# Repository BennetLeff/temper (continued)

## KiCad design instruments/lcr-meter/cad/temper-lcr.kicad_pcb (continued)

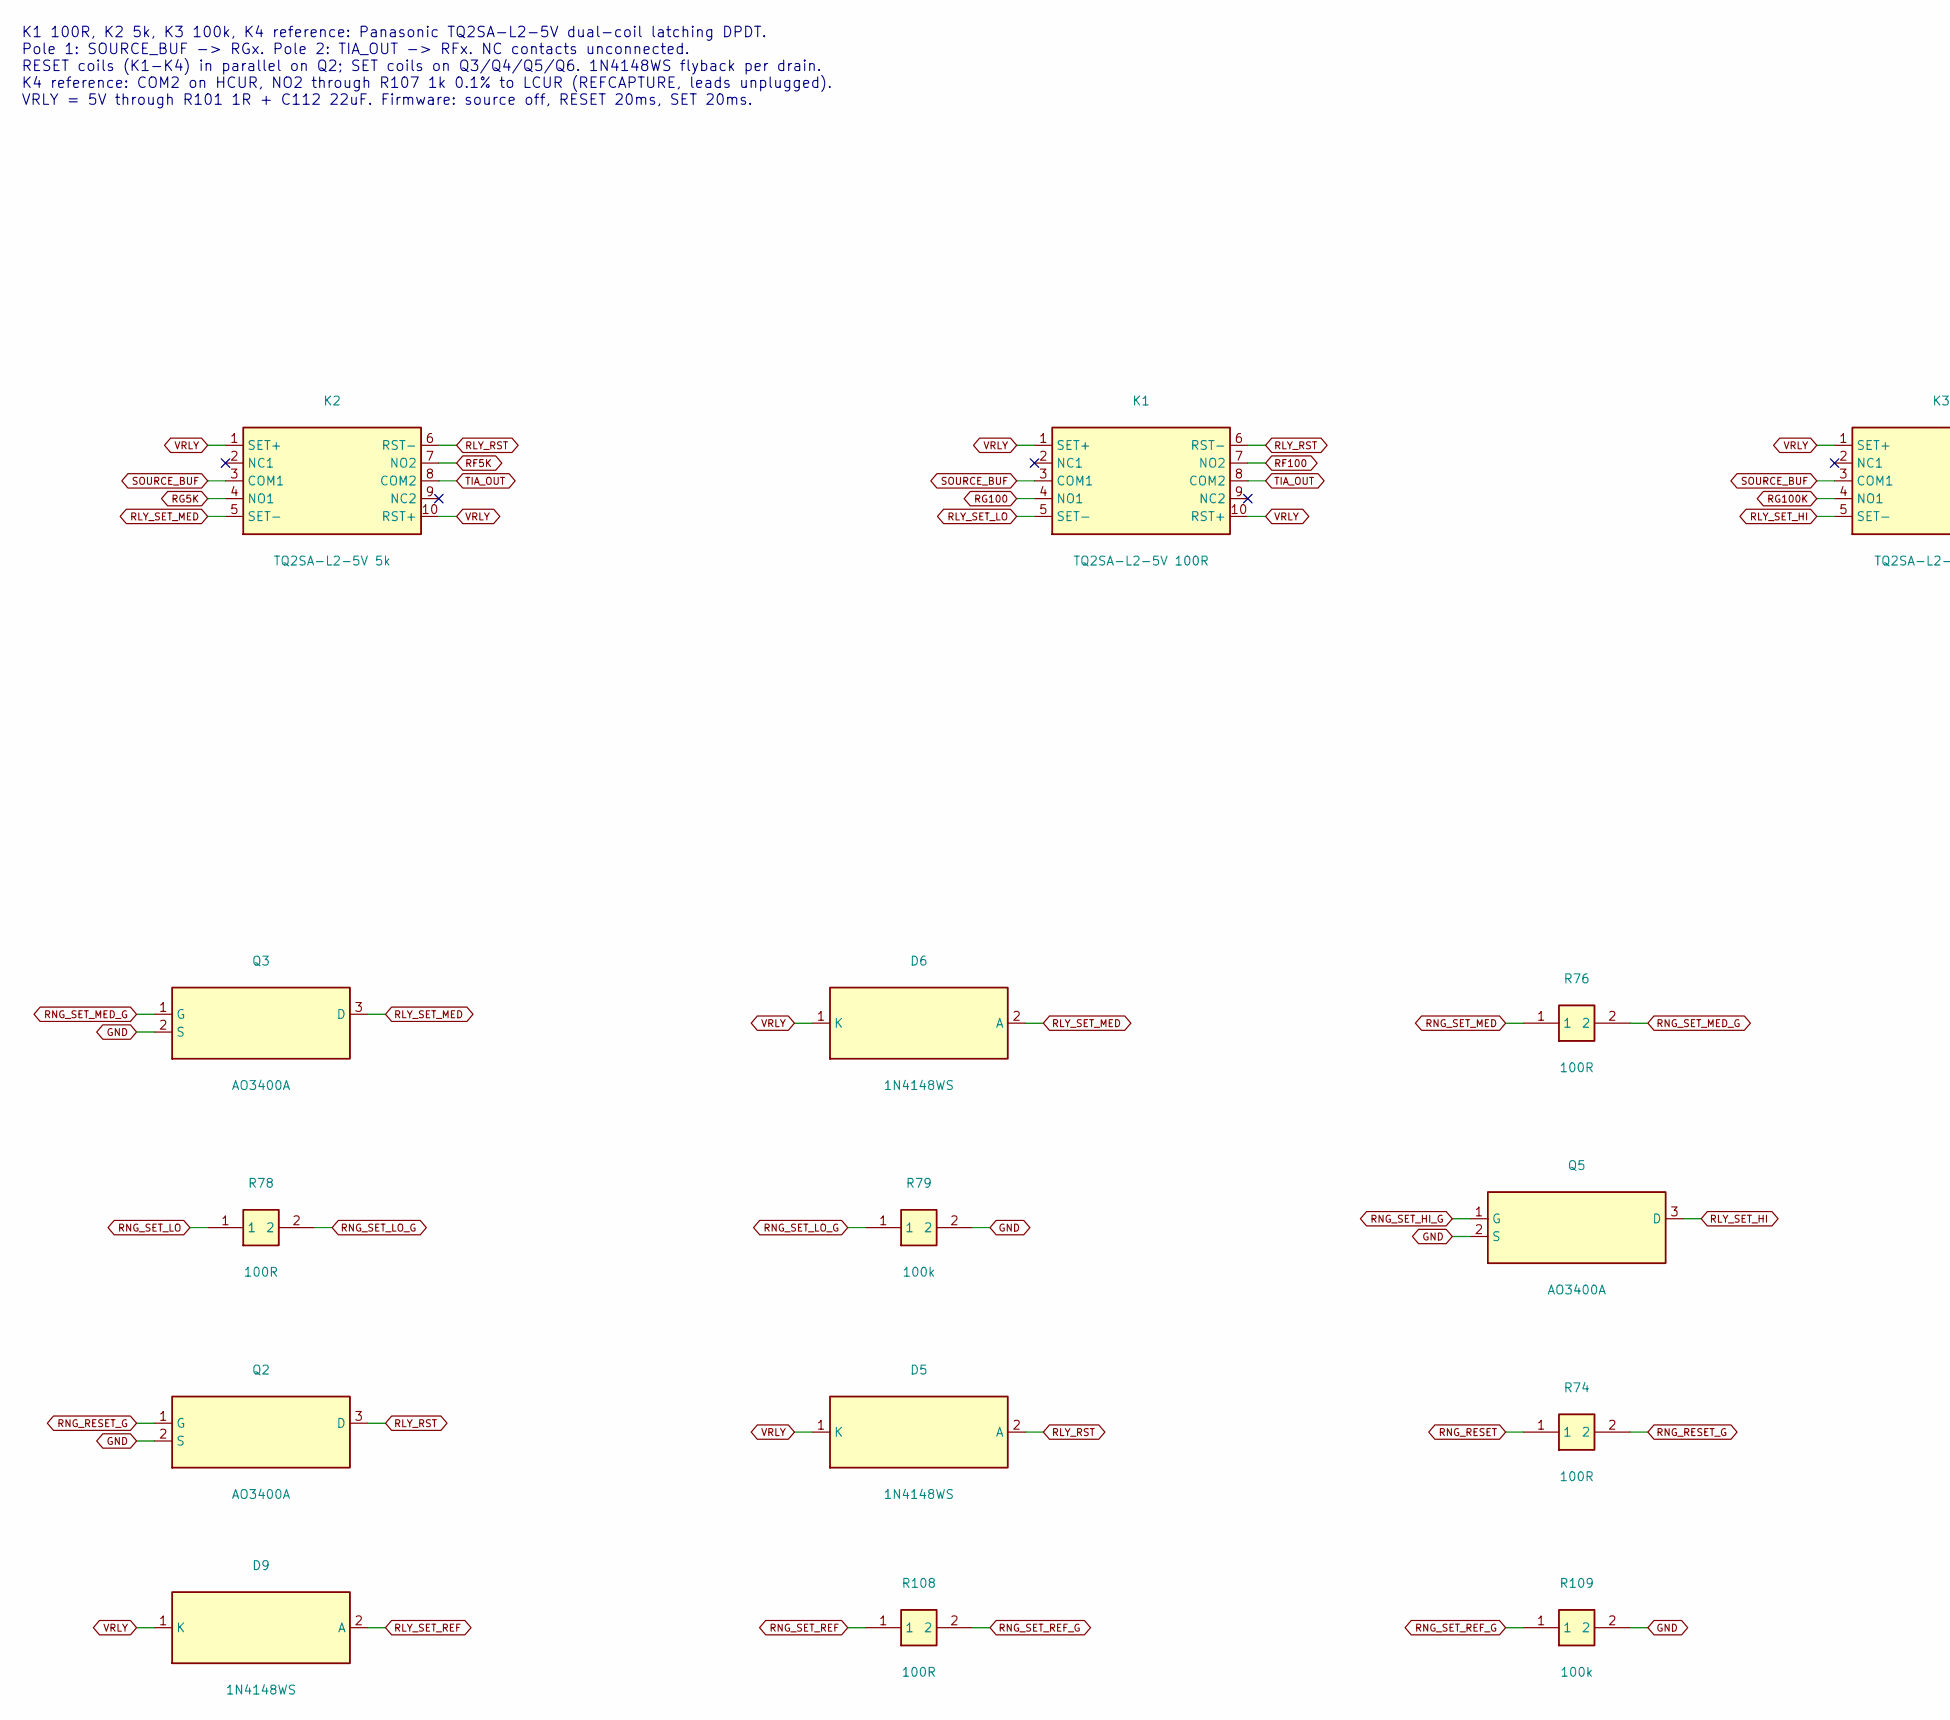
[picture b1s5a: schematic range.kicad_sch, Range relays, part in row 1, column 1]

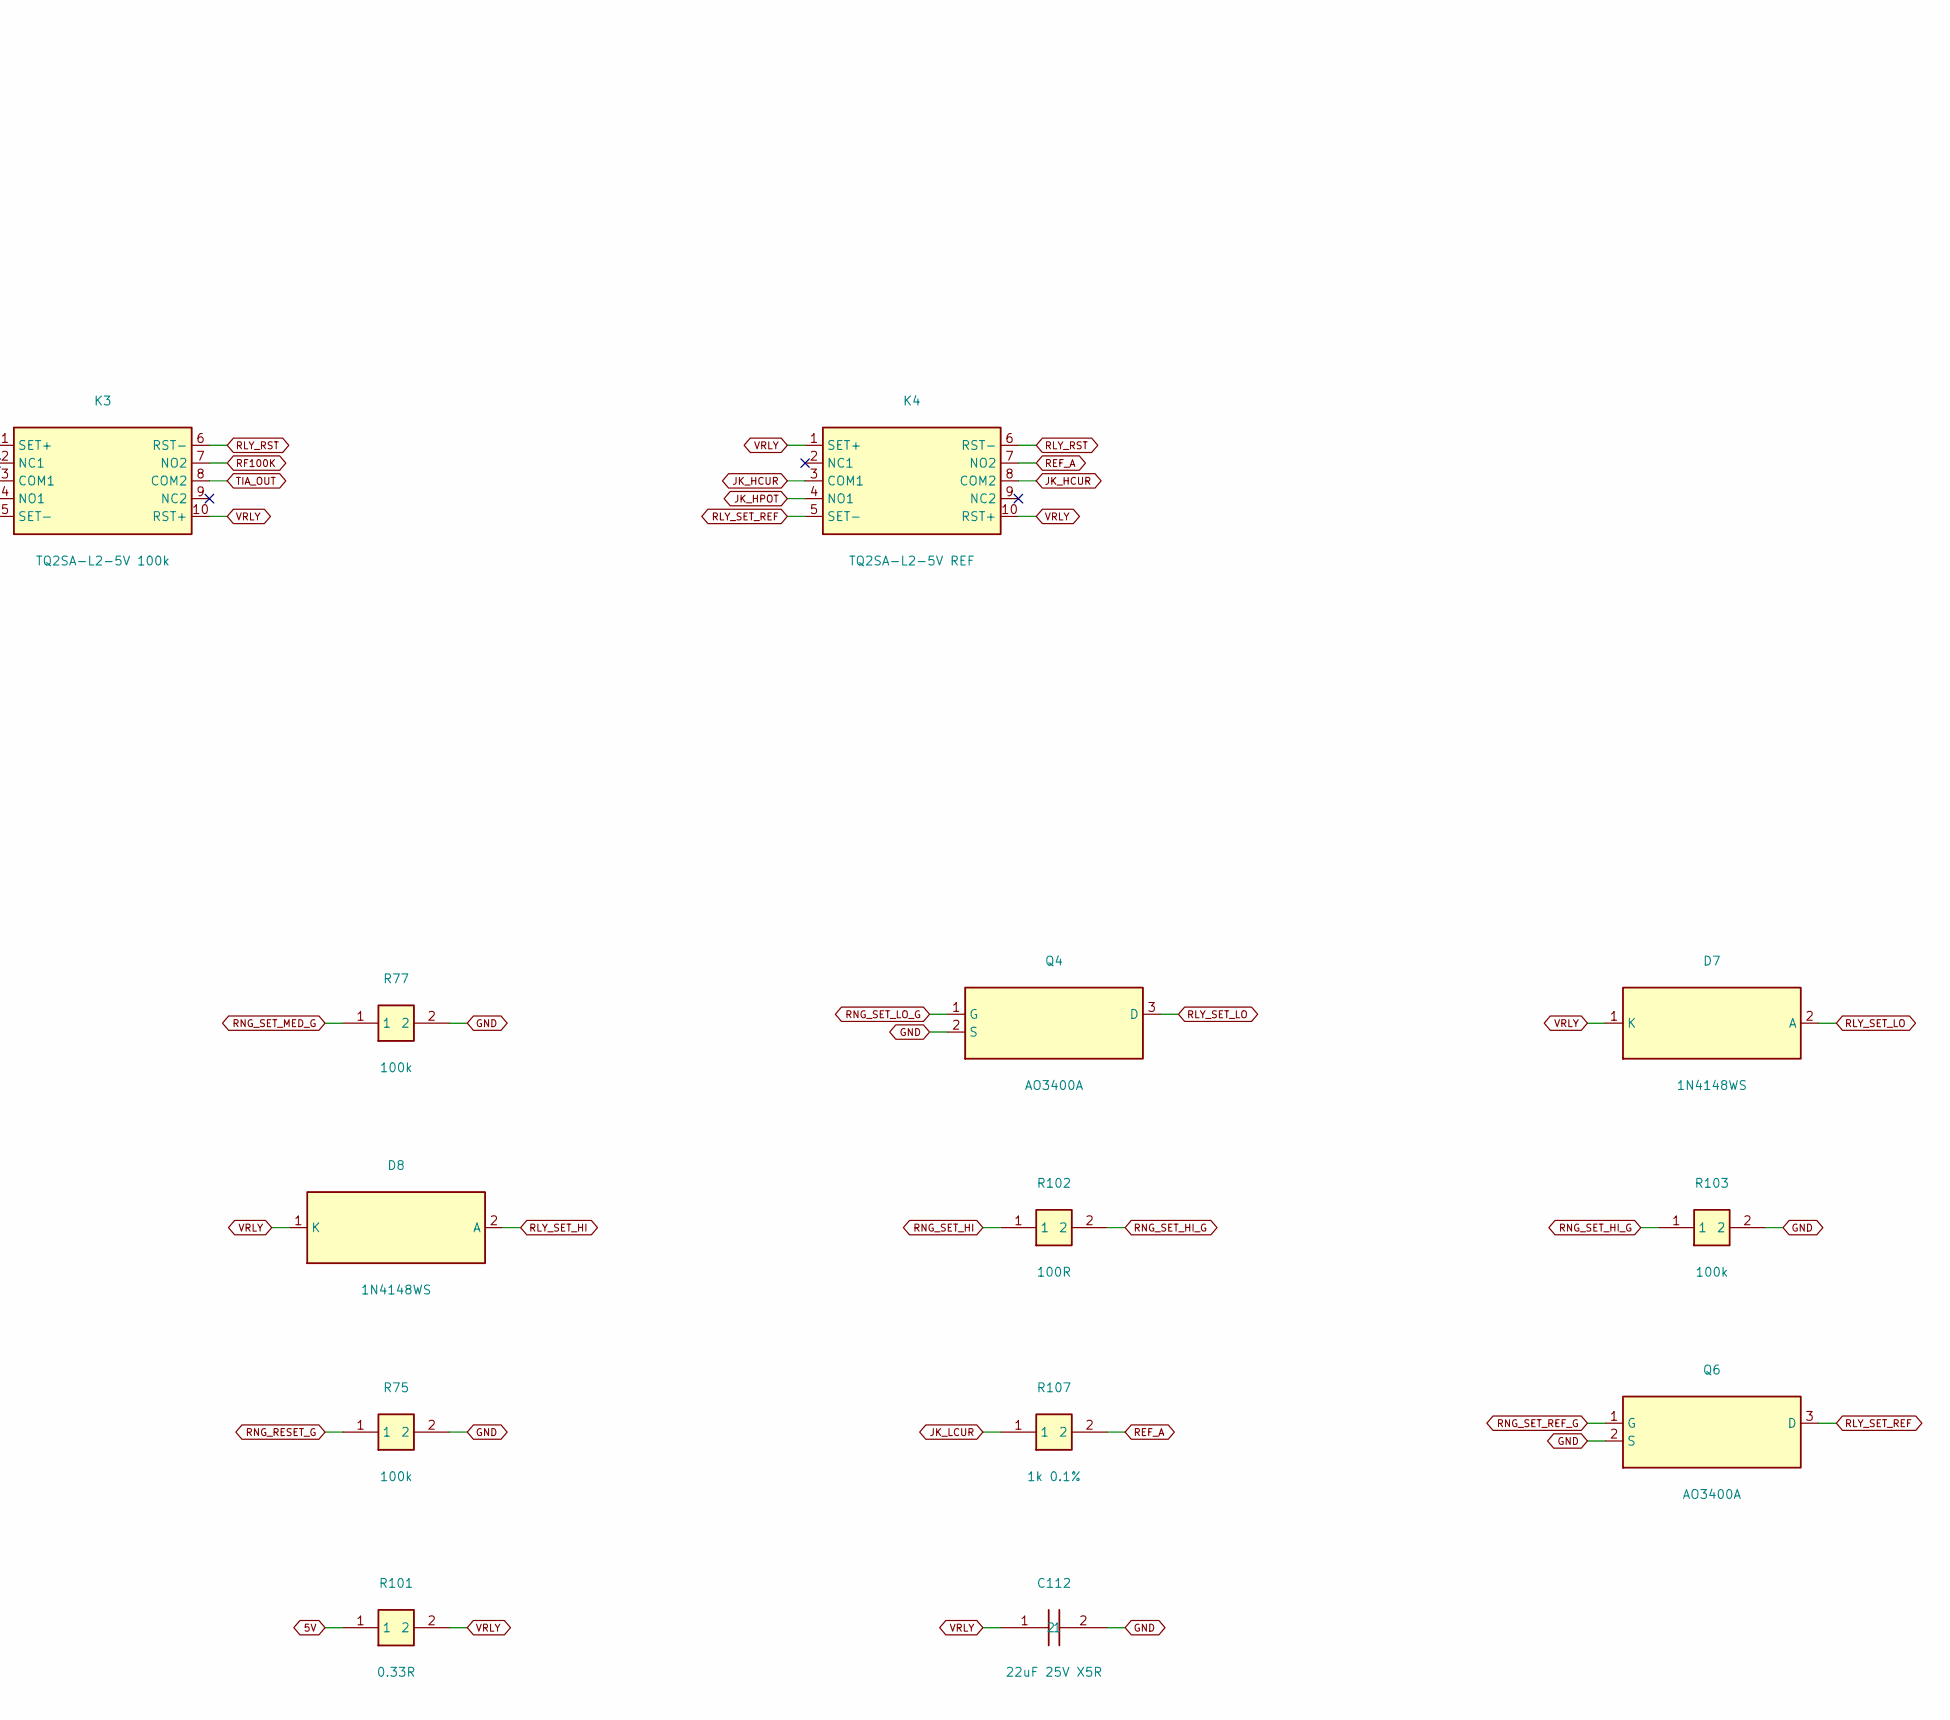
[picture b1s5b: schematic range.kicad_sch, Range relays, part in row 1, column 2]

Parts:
C112: 22uF 25V X5R; C_1206_3216Metric; MPN CL31A226KAHNNNE; LCSC C12891
D5, D6, D7, D8, D9: 1N4148WS; D_SOD-323; MPN 1N4148WS; LCSC C2128
K1: TQ2SA-L2-5V 100R; Relay_DPDT_Panasonic_TQ2SA_SMD; MPN TQ2SA-L2-5V-Z; LCSC C2684450
K2: TQ2SA-L2-5V 5k; Relay_DPDT_Panasonic_TQ2SA_SMD; MPN TQ2SA-L2-5V-Z; LCSC C2684450
K3: TQ2SA-L2-5V 100k; Relay_DPDT_Panasonic_TQ2SA_SMD; MPN TQ2SA-L2-5V-Z; LCSC C2684450
K4: TQ2SA-L2-5V REF; Relay_DPDT_Panasonic_TQ2SA_SMD; MPN TQ2SA-L2-5V-Z; LCSC C2684450
Q2, Q3, Q4, Q5, Q6: AO3400A; SOT-23; MPN AO3400A; LCSC C20917
R74, R76, R78, R102, R108: 100R; R_0603_1608Metric; MPN 0603WAF1000T5E; LCSC C22775
R75, R77, R79, R103, R109: 100k; R_0603_1608Metric; MPN 0603WAF1003T5E; LCSC C25803
R101: 0.33R; R_0603_1608Metric; MPN 0603WAF330LT5E; LCSC C23410
R107: 1k 0.1%; R_0603_1608Metric; MPN RT0603BRD071KL; LCSC C110776

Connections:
5V: R101.1; also elsewhere on the board
GND: C112.2, Q2.2 (S), Q3.2 (S), Q4.2 (S), Q5.2 (S), Q6.2 (S), R75.2, R77.2, R79.2, R103.2, R109.2; also elsewhere on the board
JK_HCUR: K4.3 (COM1), K4.8 (COM2); also elsewhere on the board
JK_HPOT: K4.4 (NO1); also elsewhere on the board
JK_LCUR: R107.1; also elsewhere on the board
REF_A: K4.7 (NO2), R107.2
RF5K: K2.7 (NO2); also elsewhere on the board
RF100: K1.7 (NO2); also elsewhere on the board
RF100K: K3.7 (NO2); also elsewhere on the board
RG5K: K2.4 (NO1); also elsewhere on the board
RG100: K1.4 (NO1); also elsewhere on the board
RG100K: K3.4 (NO1); also elsewhere on the board
RLY_RST: D5.2 (A), K1.6 (RST-), K2.6 (RST-), K3.6 (RST-), K4.6 (RST-), Q2.3 (D); also elsewhere on the board
RLY_SET_HI: D8.2 (A), K3.5 (SET-), Q5.3 (D); also elsewhere on the board
RLY_SET_LO: D7.2 (A), K1.5 (SET-), Q4.3 (D); also elsewhere on the board
RLY_SET_MED: D6.2 (A), K2.5 (SET-), Q3.3 (D); also elsewhere on the board
RLY_SET_REF: D9.2 (A), K4.5 (SET-), Q6.3 (D); also elsewhere on the board
RNG_RESET: R74.1; also elsewhere on the board
RNG_RESET_G: Q2.1 (G), R74.2, R75.1
RNG_SET_HI: R102.1; also elsewhere on the board
RNG_SET_HI_G: Q5.1 (G), R102.2, R103.1
RNG_SET_LO: R78.1; also elsewhere on the board
RNG_SET_LO_G: Q4.1 (G), R78.2, R79.1
RNG_SET_MED: R76.1; also elsewhere on the board
RNG_SET_MED_G: Q3.1 (G), R76.2, R77.1
RNG_SET_REF: R108.1; also elsewhere on the board
RNG_SET_REF_G: Q6.1 (G), R108.2, R109.1
SOURCE_BUF: K1.3 (COM1), K2.3 (COM1), K3.3 (COM1); also elsewhere on the board
TIA_OUT: K1.8 (COM2), K2.8 (COM2), K3.8 (COM2); also elsewhere on the board
VRLY: C112.1, D5.1 (K), D6.1 (K), D7.1 (K), D8.1 (K), D9.1 (K), K1.1 (SET+), K1.10 (RST+), K2.1 (SET+), K2.10 (RST+), K3.1 (SET+), K3.10 (RST+), K4.1 (SET+), K4.10 (RST+), R101.2; also elsewhere on the board

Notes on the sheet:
K1 100R, K2 5k, K3 100k, K4 reference: Panasonic TQ2SA-L2-5V dual-coil latching DPDT. Pole 1: SOURCE_BUF -> RGx. Pole 2: TIA_OUT -> RFx. NC contacts unconnected. RESET coils (K1-K4) in parallel on Q2; SET coils on Q3/Q4/Q5/Q6. 1N4148WS flyback per drain. K4 reference: COM2 on HCUR, NO2 through R107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

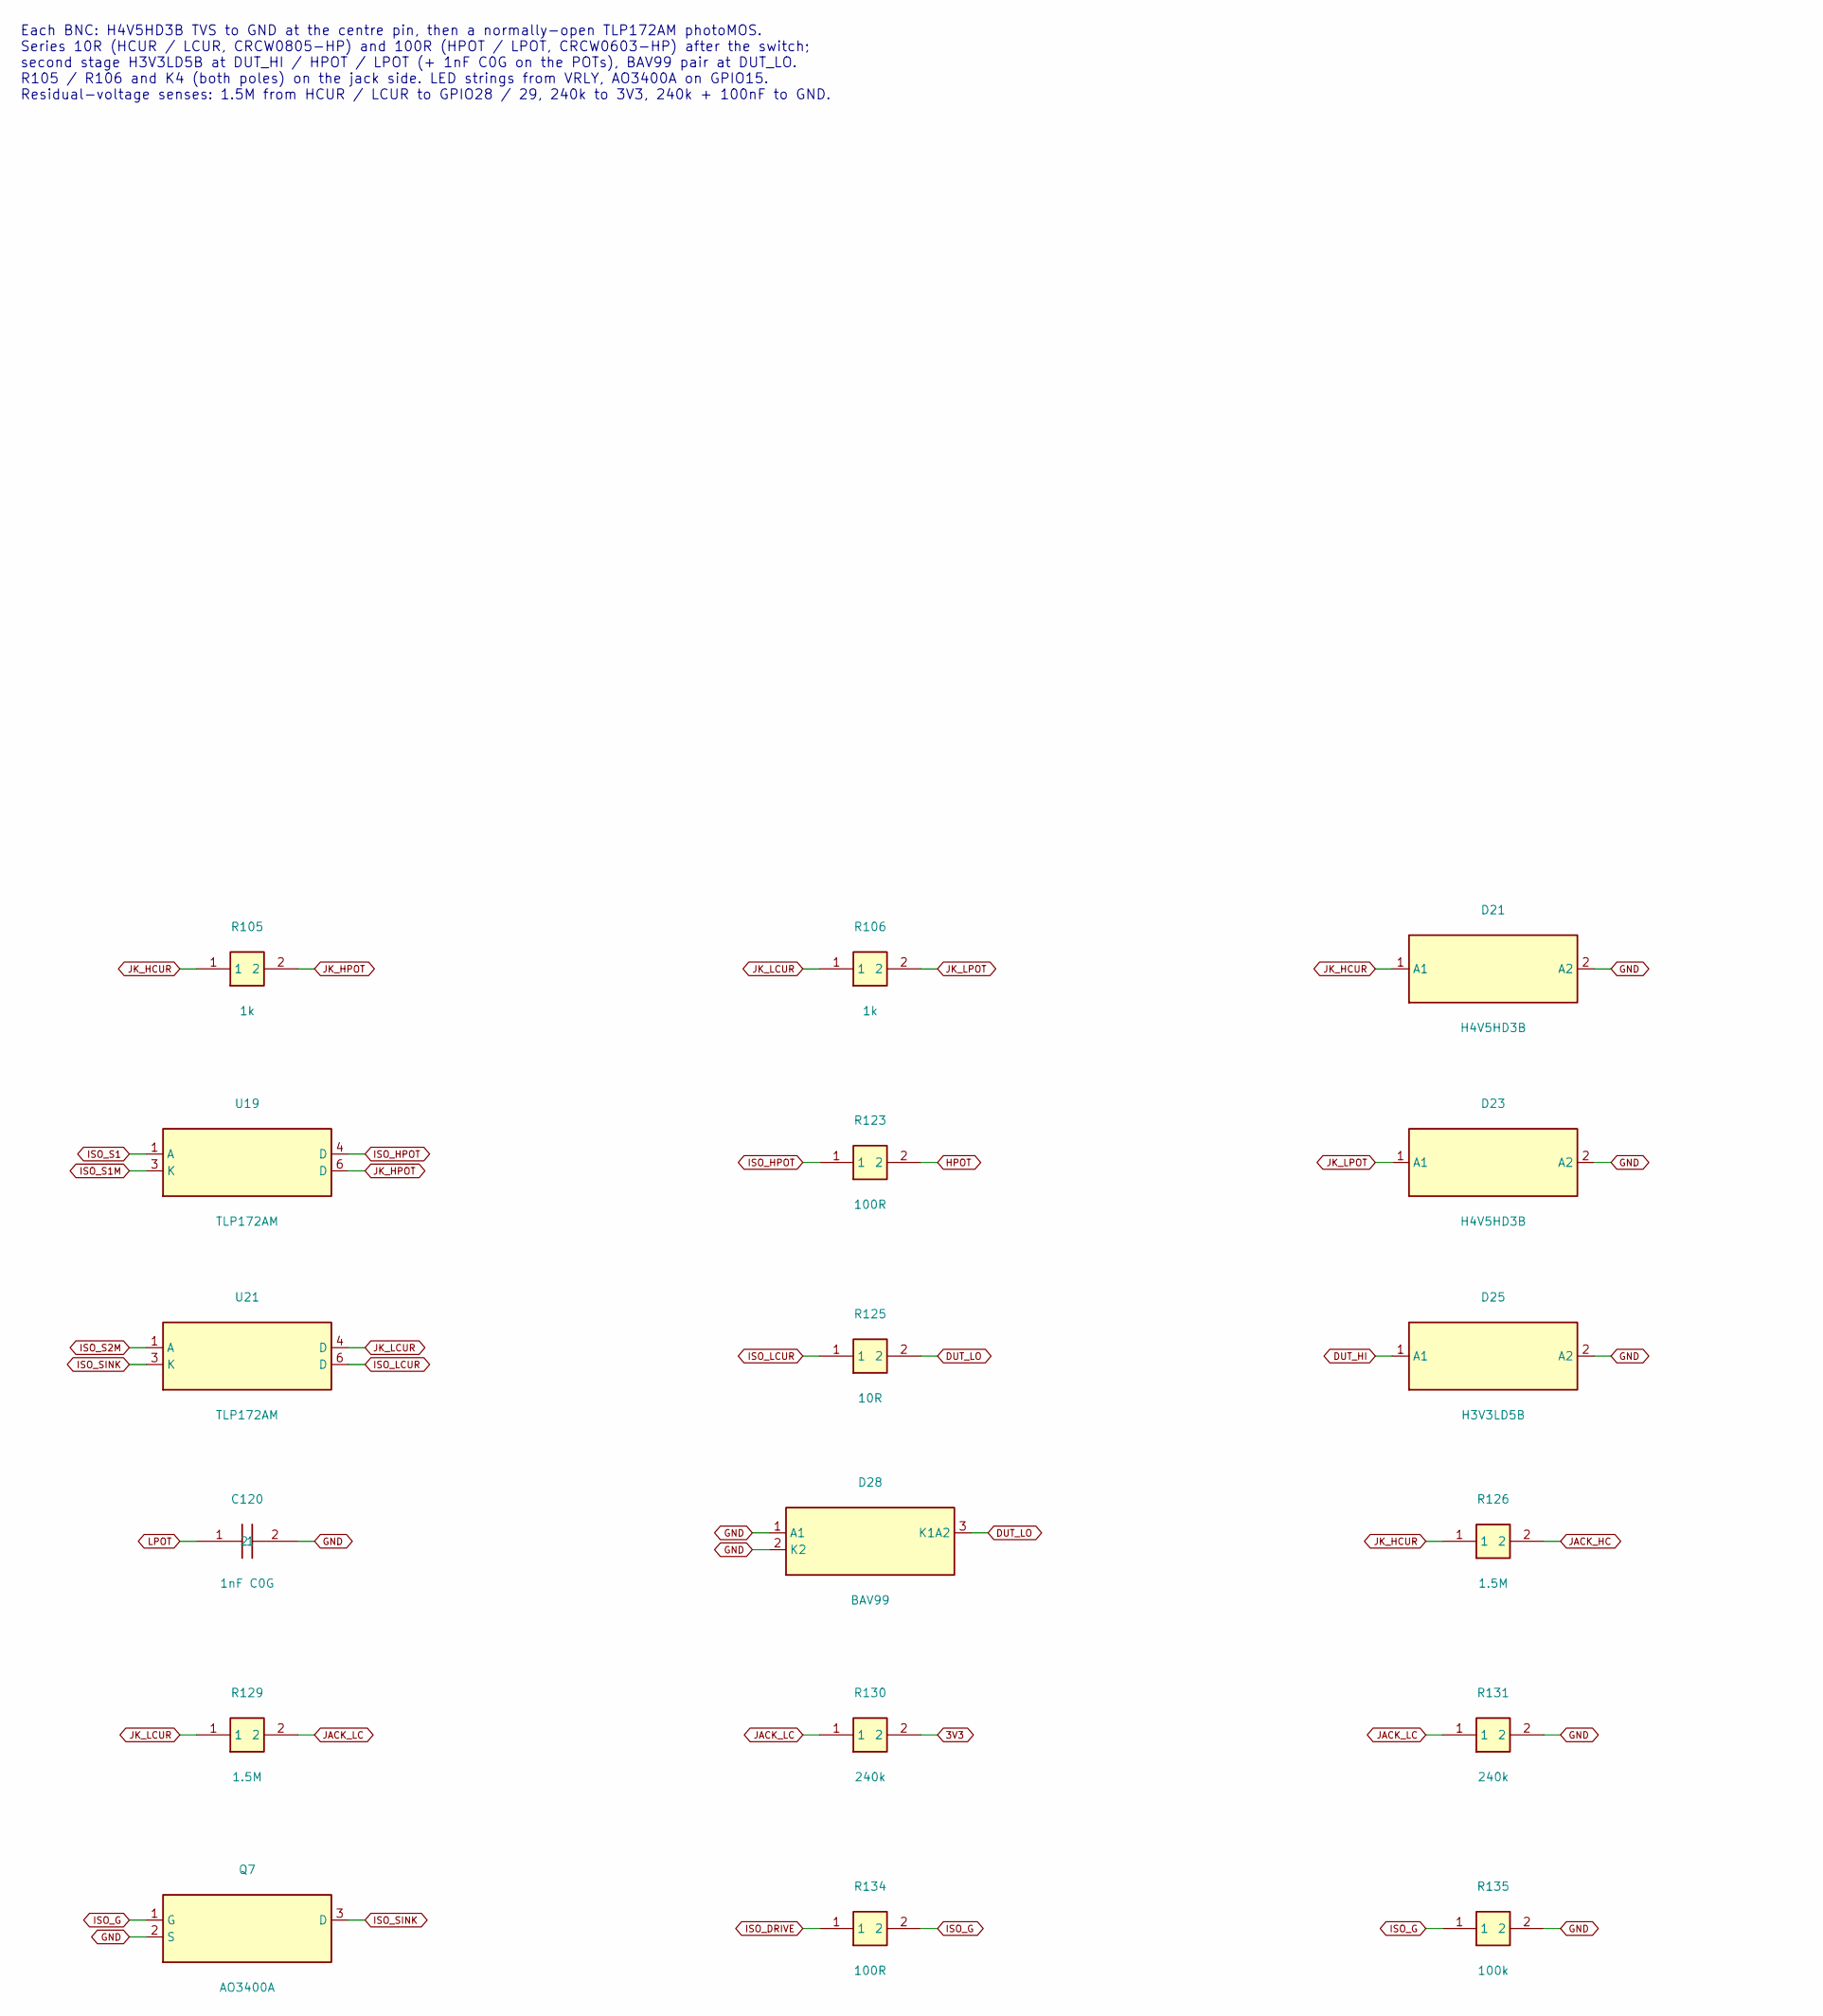
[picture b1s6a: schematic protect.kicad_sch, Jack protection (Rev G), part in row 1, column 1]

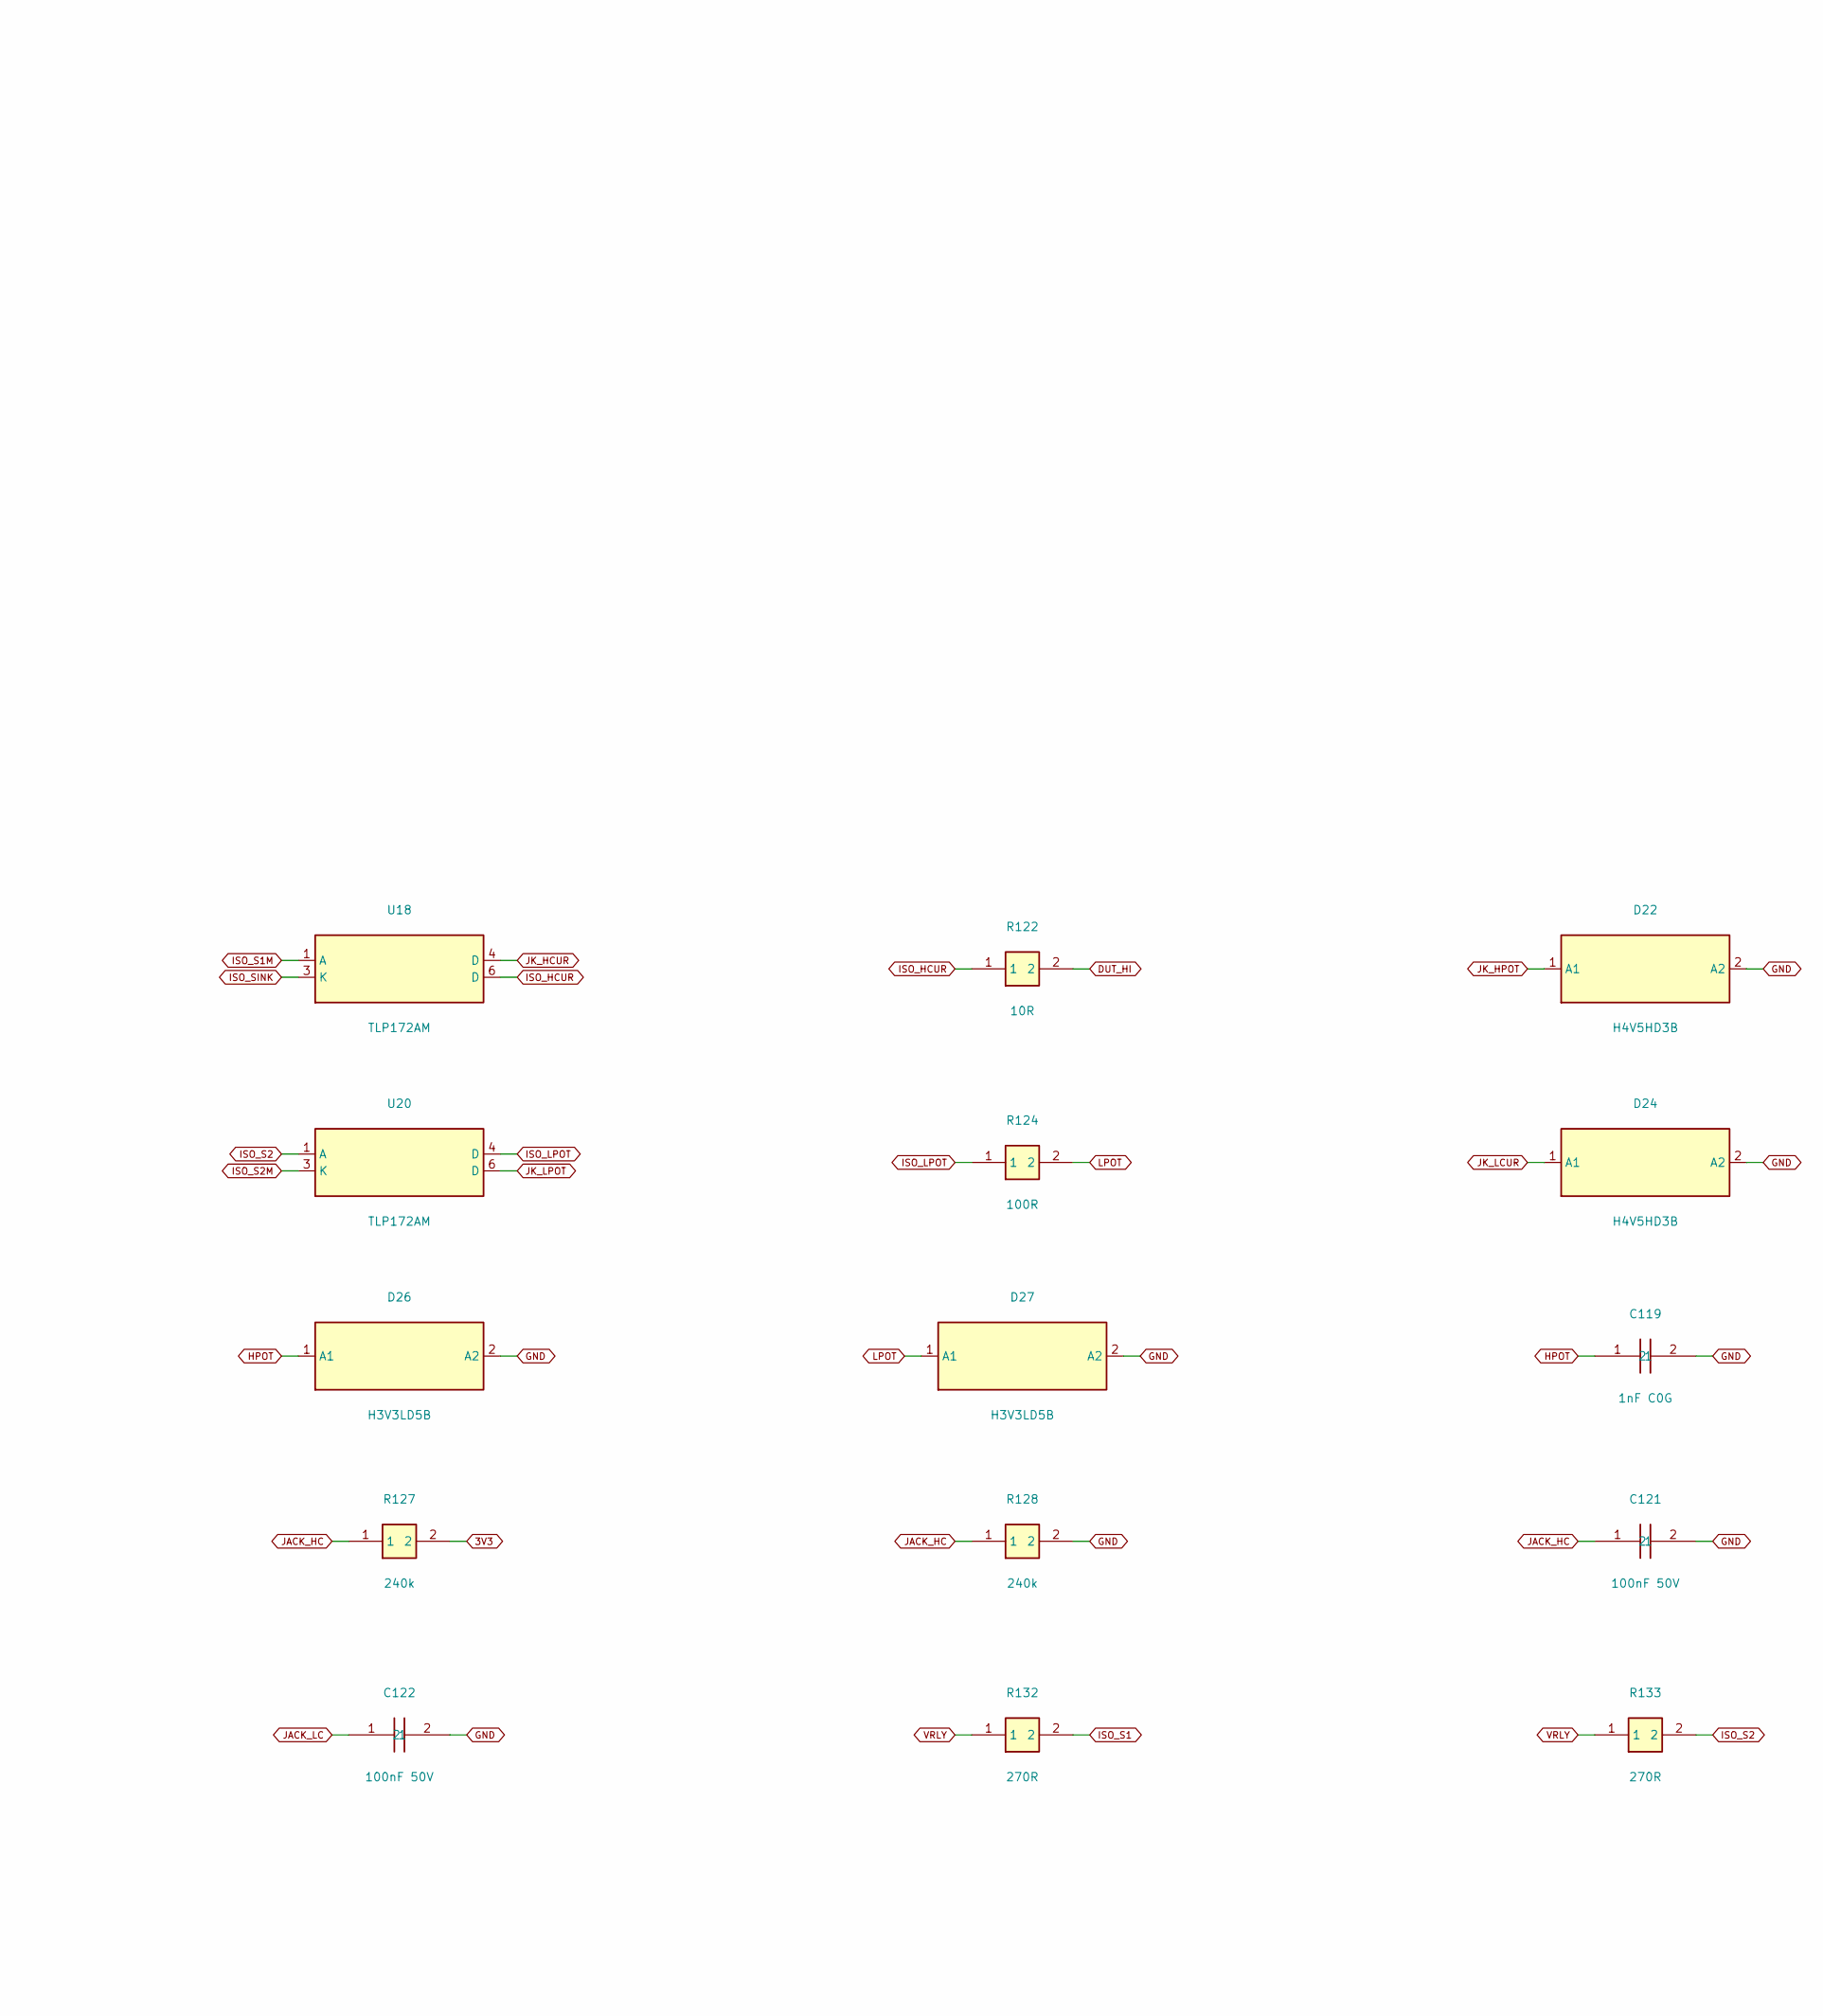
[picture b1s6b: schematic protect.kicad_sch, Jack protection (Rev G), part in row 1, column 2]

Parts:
C119, C120: 1nF C0G; C_0603_1608Metric; MPN CC0603JRNPO9BN102; LCSC C106246
C121, C122: 100nF 50V; C_0603_1608Metric; MPN CC0603KRX7R9BB104; LCSC C14663
D21, D22, D23, D24: H4V5HD3B; D_SOD-323_HJC; MPN H4V5HD3B; LCSC C20615803
D25, D26, D27: H3V3LD5B; D_SOD-523; MPN H3V3LD5B; LCSC C20615817
D28: BAV99; SOT-23; MPN BAV99,215; LCSC C2500
Q7: AO3400A; SOT-23; MPN AO3400A; LCSC C20917
R105, R106: 1k; R_0603_1608Metric; MPN 0603WAF1001T5E; LCSC C21190
R122, R125: 10R; R_0805_2012Metric; MPN CRCW080510R0FKEAHP; LCSC C844598
R123, R124: 100R; R_0603_1608Metric; MPN CRCW0603100RFKEAHP; LCSC C844725
R126, R129: 1.5M; R_0603_1608Metric; MPN 0603WAF1504T5E; LCSC C4172
R127, R128, R130, R131: 240k; R_0603_1608Metric; MPN 0603WAF2403T5E; LCSC C4197
R132, R133: 270R; R_0603_1608Metric; MPN 0603WAF2700T5E; LCSC C22966
R134: 100R; R_0603_1608Metric; MPN 0603WAF1000T5E; LCSC C22775
R135: 100k; R_0603_1608Metric; MPN 0603WAF1003T5E; LCSC C25803
U18, U19, U20, U21: TLP172AM; Toshiba_11-4M1S; MPN TLP172AM(TPL,E); LCSC C2152276

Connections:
3V3: R127.2, R130.2; also elsewhere on the board
DUT_HI: D25.1 (A1), R122.2; also elsewhere on the board
DUT_LO: D28.3 (K1A2), R125.2; also elsewhere on the board
GND: C119.2, C120.2, C121.2, C122.2, D21.2 (A2), D22.2 (A2), D23.2 (A2), D24.2 (A2), D25.2 (A2), D26.2 (A2), D27.2 (A2), D28.1 (A1), D28.2 (K2), Q7.2 (S), R128.2, R131.2, R135.2; also elsewhere on the board
HPOT: C119.1, D26.1 (A1), R123.2; also elsewhere on the board
ISO_DRIVE: R134.1; also elsewhere on the board
ISO_G: Q7.1 (G), R134.2, R135.1
ISO_HCUR: R122.1, U18.6 (D)
ISO_HPOT: R123.1, U19.4 (D)
ISO_LCUR: R125.1, U21.6 (D)
ISO_LPOT: R124.1, U20.4 (D)
ISO_S1: R132.2, U19.1 (A)
ISO_S1M: U18.1 (A), U19.3 (K)
ISO_S2: R133.2, U20.1 (A)
ISO_S2M: U20.3 (K), U21.1 (A)
ISO_SINK: Q7.3 (D), U18.3 (K), U21.3 (K)
JACK_HC: C121.1, R126.2, R127.1, R128.1; also elsewhere on the board
JACK_LC: C122.1, R129.2, R130.1, R131.1; also elsewhere on the board
JK_HCUR: D21.1 (A1), R105.1, R126.1, U18.4 (D); also elsewhere on the board
JK_HPOT: D22.1 (A1), R105.2, U19.6 (D); also elsewhere on the board
JK_LCUR: D24.1 (A1), R106.1, R129.1, U21.4 (D); also elsewhere on the board
JK_LPOT: D23.1 (A1), R106.2, U20.6 (D); also elsewhere on the board
LPOT: C120.1, D27.1 (A1), R124.2; also elsewhere on the board
VRLY: R132.1, R133.1; also elsewhere on the board

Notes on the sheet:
Each BNC: H4V5HD3B TVS to GND at the centre pin, then a normally-open TLP172AM photoMOS. Series 10R (HCUR / LCUR, CRCW0805-HP) and 100R (HPOT / LPOT, CRCW0603-HP) after the switch; second stage H3V3LD5B at DUT_HI / HPOT / LPOT (+ 1nF C0G on the POTs), BAV99 pair at DUT_LO. R105 / R106 and K4 (both 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
